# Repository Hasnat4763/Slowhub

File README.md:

# Slowhub

A USB 2.0 hub based on the SL2.1A

# Why did I make it

I had designed another USB 2.0 hub with the same chip before, but I did not have a lot of experience Back then so when I received the PCB, the hub was not fully working, the audio Input/Output part was working great but It could not handle connecting USB peripherals like Pendrives and Keyboard/Mouse. So I decided to design another USB Hub with it to fix the past mistakes. 

# Gallery

## PCB

# Schematic

# PCB

# Case

# BOM

| Part name | Quantity | Price | Product Link |
|--------------------------------------------------|----------|----------------|------|
| SL2.A USB HUB IC | 5 | $1.40 | [Link](https://www.aliexpress.com/item/1005005552905296.html) |
| USB A Female Port | 10 | $5.68 | [Link](https://www.aliexpress.com/item/1005010243685669.html) |
| USB C Female Port (TYPE-C-02) | 10 | $2.06 | [Link](https://www.aliexpress.com/item/1005005371954812.html) |
| Capacitor Kit (0.1uF, 1uf, 10uF) | 1 | $3.67 | [Link](https://www.aliexpress.com/item/1005007293819361.html) |
| 5.1k Resistor 0603 | 100 | $1.73 | [Link](https://www.aliexpress.com/item/1005008152622017.html) |
| PCB | 5 | $0.18 | JLCPCB |
| 3D printed Case Parts | 2 | Printing Legion | Printing Legion HC |

# Build instruction

You will have to use SMD soldering for soldering 90% of the parts. you may need a stencil if you want to use a hot plate, but a soldering iron can be used too.

# Zine

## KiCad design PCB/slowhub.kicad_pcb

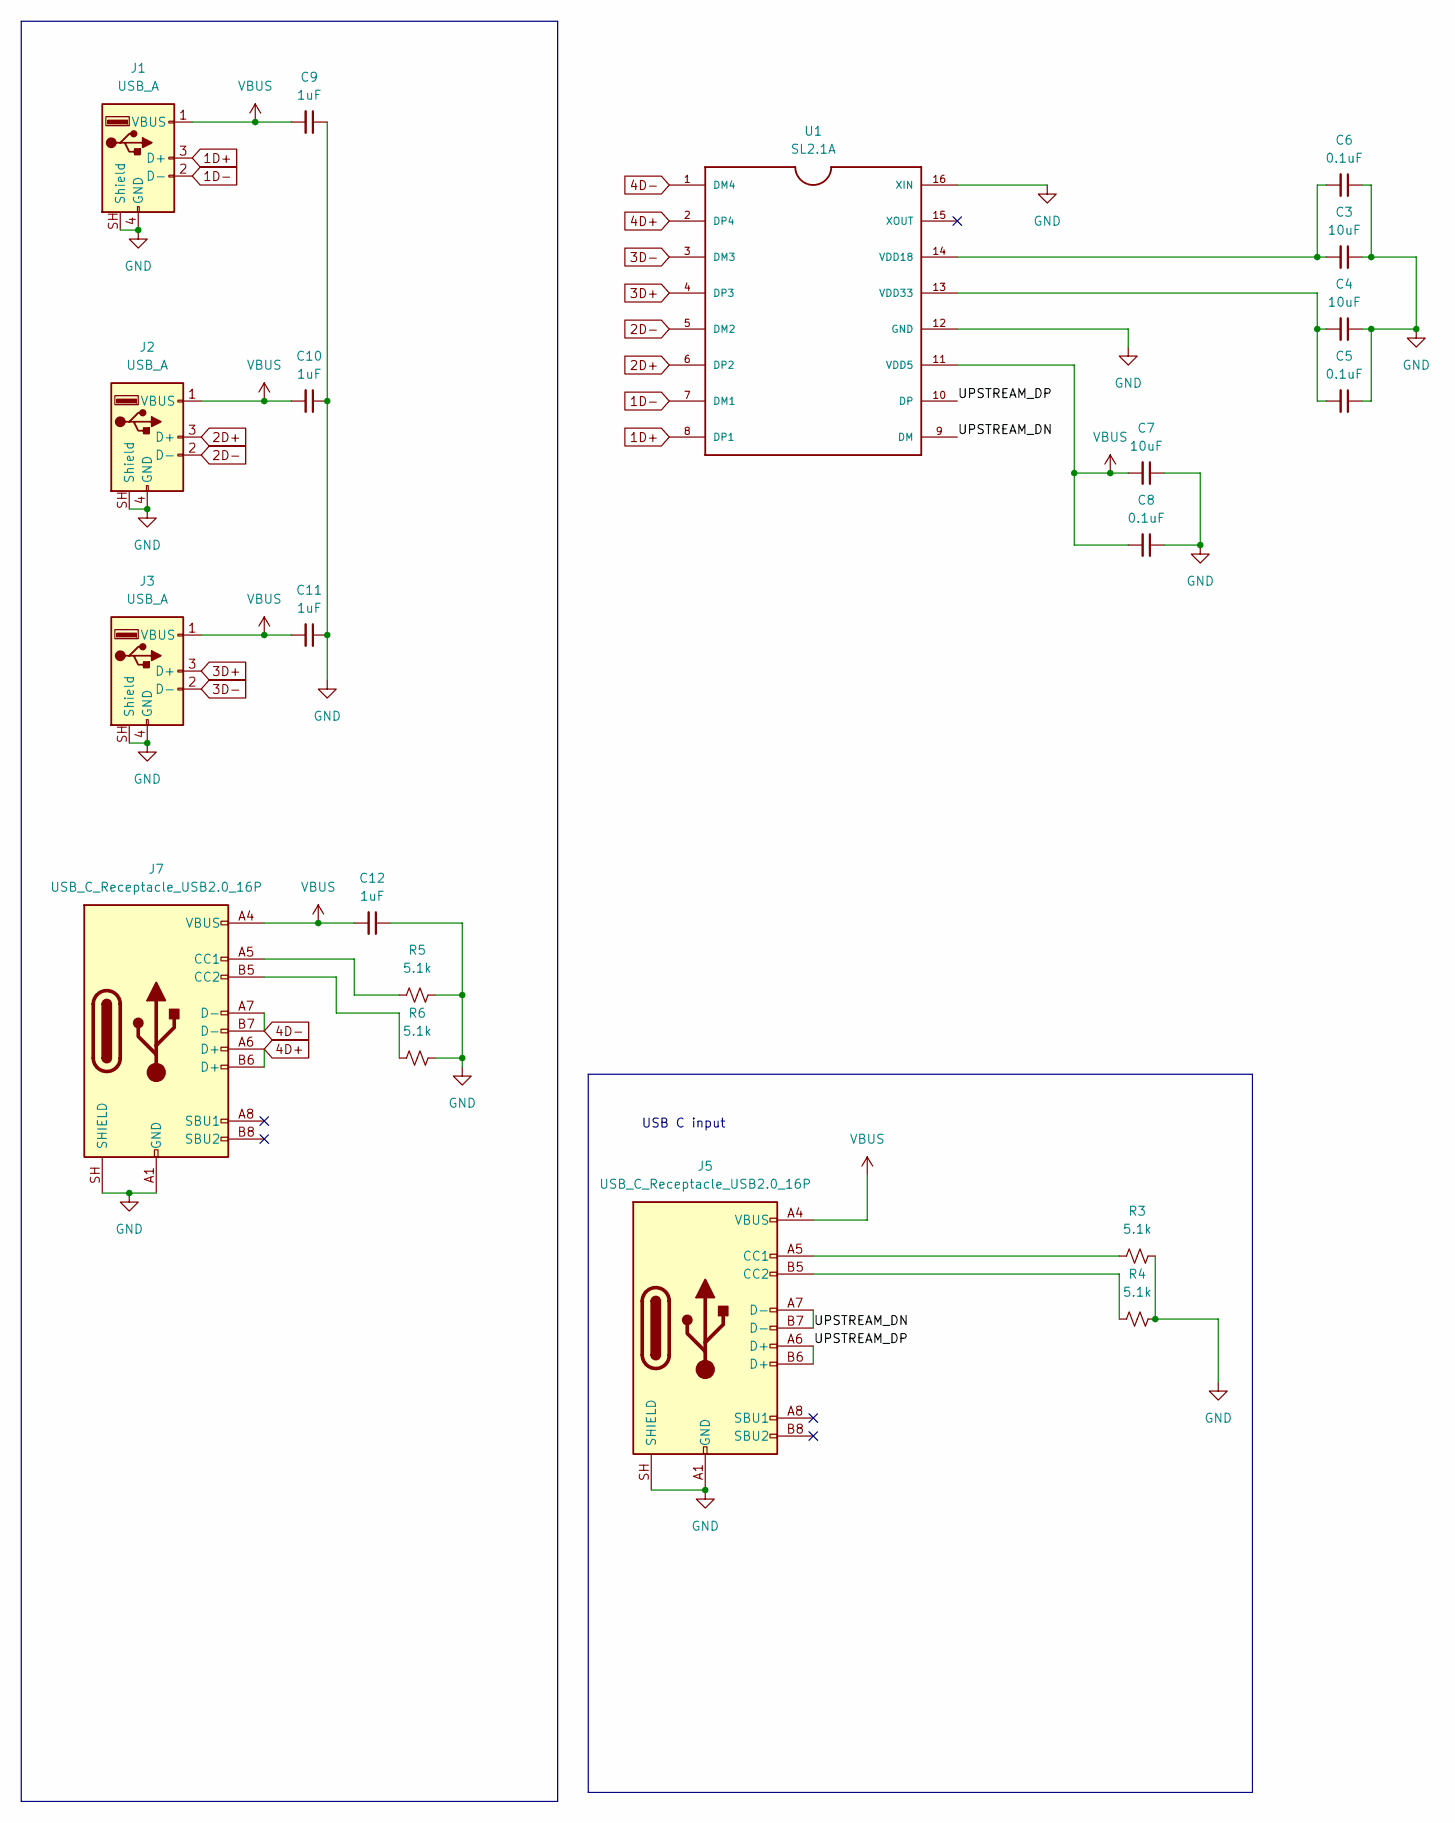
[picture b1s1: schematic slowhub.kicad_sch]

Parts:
C3, C4, C7: 10uF; C_0603_1608Metric_Pad1.08x0.95mm_HandSolder
C5, C6, C8: 0.1uF; C_0603_1608Metric_Pad1.08x0.95mm_HandSolder
C9, C10, C11, C12: 1uF; C_0603_1608Metric_Pad1.08x0.95mm_HandSolder
J1, J2, J3: USB_A; USB_A_TE_292303-7_Horizontal
J5, J7: USB_C_Receptacle_USB2.0_16P; USB_C_Receptacle_GCT_USB4105-xx-A_16P_TopMnt_Horizontal
R3, R4, R5, R6: 5.1k; R_0603_1608Metric_Pad0.98x0.95mm_HandSolder
U1: SL2.1A; SO16

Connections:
1D+: J1.3 (D+), U1.8 (DP1)
1D-: J1.2 (D-), U1.7 (DM1)
2D+: J2.3 (D+), U1.6 (DP2)
2D-: J2.2 (D-), U1.5 (DM2)
3D+: J3.3 (D+), U1.4 (DP3)
3D-: J3.2 (D-), U1.3 (DM3)
4D+: J7.A6 (D+), J7.B6 (D+), U1.2 (DP4)
4D-: J7.A7 (D-), J7.B7 (D-), U1.1 (DM4)
/UPSTREAM_DN: J5.A7 (D-), J5.B7 (D-), U1.9 (DM)
/UPSTREAM_DP: J5.A6 (D+), J5.B6 (D+), U1.10 (DP)
GND: C3.1, C4.1, C5.1, C6.1, C7.1, C8.1, C9.1, C10.1, C11.1, C12.1, J1.4 (GND), J1.SH (Shield), J2.4 (GND), J2.SH (Shield), J3.4 (GND), J3.SH (Shield), J5.A1 (GND), J5.A12 (GND), J5.B1 (GND), J5.B12 (GND), J5.SH (SHIELD), J7.A1 (GND), J7.A12 (GND), J7.B1 (GND), J7.B12 (GND), J7.SH (SHIELD), R3.2, R4.2, R5.2, R6.2, U1.12 (GND), U1.16 (XIN)
unnamed: J5.A5 (CC1), R3.1
unnamed: J5.B5 (CC2), R4.1
unnamed: J7.A5 (CC1), R5.1
unnamed: J7.B5 (CC2), R6.1
unnamed: C3.2, C6.2, U1.14 (VDD18)
unnamed: C4.2, C5.2, U1.13 (VDD33)
VBUS: C7.2, C8.2, C9.2, C10.2, C11.2, C12.2, J1.1 (VBUS), J2.1 (VBUS), J3.1 (VBUS), J5.A4 (VBUS), J5.A9 (VBUS), J5.B4 (VBUS), J5.B9 (VBUS), J7.A4 (VBUS), J7.A9 (VBUS), J7.B4 (VBUS), J7.B9 (VBUS), U1.11 (VDD5)

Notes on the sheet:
USB C input

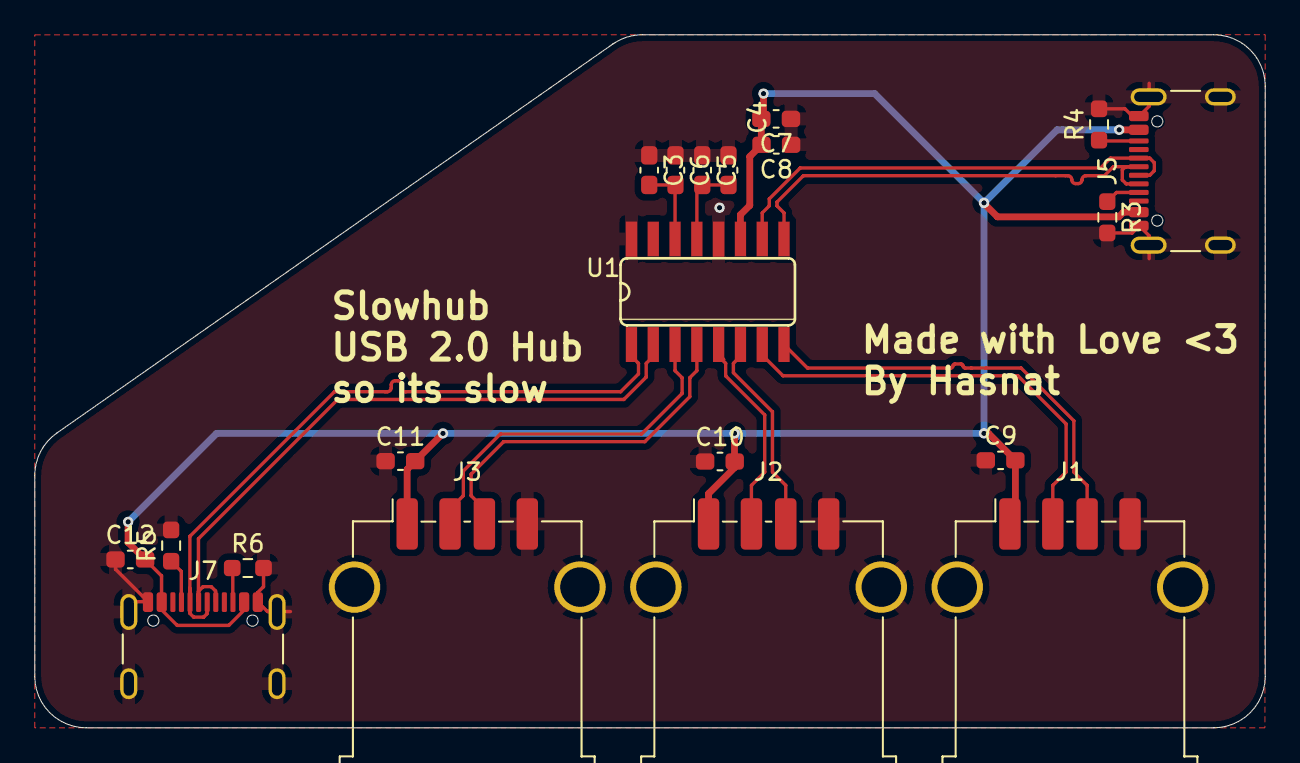
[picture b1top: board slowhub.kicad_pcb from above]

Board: 2 copper layers, 71.7 x 40.4 mm, 20 parts (0 on the bottom side), 18 nets.

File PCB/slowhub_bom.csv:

Designator,Footprint,Quantity,Value,LCSC Part #
"C10, C11, C12, C9",0603,4,1uF,
"C3, C4, C7",0603,3,10uF,
"C5, C6, C8",0603,3,0.1uF,
"J1, J2, J3",USB_A_TE_292303-7_Horizontal,3,USB_A,
"J5, J7",USB_C_Receptacle_GCT_USB4105-xx-A_16P_TopMnt_Horizontal,2,USB_C_Receptacle_USB2.0_16P,
"R3, R4, R5, R6",0603,4,5.1k,
U1,SO16,1,SL2.1A,

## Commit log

2026-06-03 Add stuff
2026-06-03 BOM Markdown fixing
